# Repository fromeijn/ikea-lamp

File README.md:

# ikea-lamp
make and ikea lamp smart and awesome

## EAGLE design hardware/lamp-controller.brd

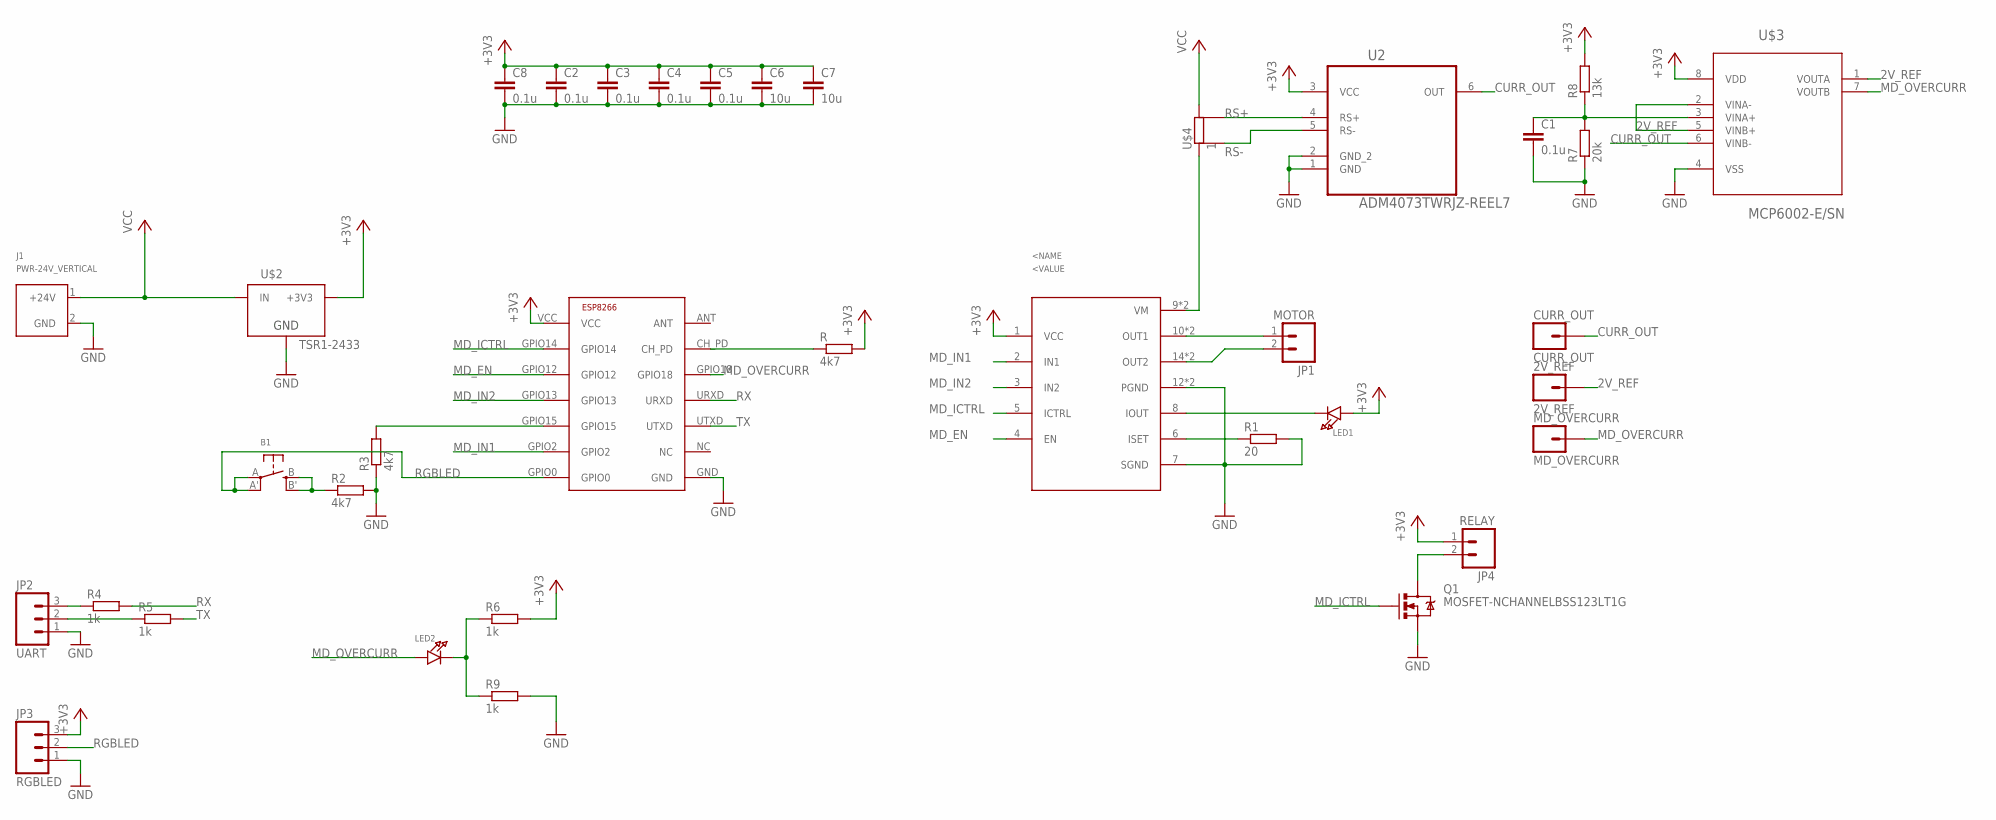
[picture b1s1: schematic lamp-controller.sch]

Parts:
2V_REF: 2V_REF; 1X01
B1: SWITCH_TACT_SMT; EVQ-Q2
C1, C2, C3, C4, C5, C8: 0.1u; C0805
C6, C7: 10u; C0805
CURR_OUT: CURR_OUT; 1X01
J1: PWR-24V_VERTICAL; PHOENIX-CONTACT-MCV-1,5/2-G-3,81
JP1: MOTOR; 1X02
JP2: UART; 1X03_LOCK
JP3: RGBLED; 1X03_LOCK
JP4: RELAY; 1X02
LED1, LED2: LED1206; CHIPLED_1206
MD_OVERCURR: MD_OVERCURR; 1X01
Q1: MOSFET-NCHANNELBSS123LT1G; SOT23
R, R2, R3: 4k7; R0805
R1: 20; R0805
R4, R5, R6, R9: 1k; R0805
R7: 20k; R0805
R8: 13k; R0805
U1: LV8400V; TSSOP16
U2: ADM4073TWRJZ-REEL7; SOT95P280X145-6N
U$1: ESP8266-03; ESP-03
U$2: TSR1-2433; TSR-1
U$3: MCP6002-E/SN; SOIC127P600X175-8N
U$4: 1; R2512

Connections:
2V_REF: 2V_REF.1, U$3.1 (VOUTA), U$3.2 (VINA-), U$3.5 (VINB+)
+3V3: C2.1, C3.1, C4.1, C5.1, C6.1, C7.1, C8.1, JP3.3, JP4.1, LED1.A, R.2, R6.2, R8.2, U1.1 (VCC), U2.3 (VCC), U$1.VCC, U$2.3 (+3V3), U$3.8 (VDD)
CURR_OUT: CURR_OUT.1, U2.6 (OUT), U$3.6 (VINB-)
GND: C1.2, C2.2, C3.2, C4.2, C5.2, C6.2, C7.2, C8.2, J1.2 (GND), JP2.1, JP3.1, Q1.2 (S), R1.2, R2.2, R3.1, R7.1, R9.2, U1.7 (SGND), U1.12 (PGND), U1.13 (PGND), U2.2 (GND_2), U$1.GND, U$2.2 (GND), U$3.4 (VSS)
MD_EN: U1.4 (EN), U$1.GPIO12
MD_ICTRL: Q1.1 (G), U1.5 (ICTRL), U$1.GPIO14
MD_IN1: U1.2 (IN1), U$1.GPIO2
MD_IN2: U1.3 (IN2), U$1.GPIO13
MD_OVERCURR: LED2.A, MD_OVERCURR.1, U$1.GPIO18, U$3.7 (VOUTB)
unnamed: LED1.C, U1.8 (IOUT)
unnamed: R1.1, U1.6 (ISET)
unnamed: B1.B (S), B1.B' (S1), R2.1
unnamed: R3.2, U$1.GPIO15
unnamed: JP1.1, U1.10 (OUT1), U1.11 (OUT1)
unnamed: JP1.2, U1.14 (OUT2), U1.15 (OUT2)
unnamed: U1.9 (VM), U1.16 (VM), U$4.1
unnamed: JP2.2, R5.1
unnamed: R.1, U$1.CH_PD
unnamed: JP2.3, R4.1
unnamed: C1.1, R7.2, R8.1, U$3.3 (VINA+)
unnamed: LED2.C, R6.1, R9.1
unnamed: JP4.2, Q1.3 (D)
RGBLED: B1.A, B1.A' (P1), JP3.2, U$1.GPIO0
RS+: U2.4 (RS+), U$4.4
RS-: U2.5 (RS-), U$4.3
RX: R4.2, U$1.URXD
TX: R5.2, U$1.UTXD
VCC: J1.1 (+24V), U$2.1 (IN), U$4.2

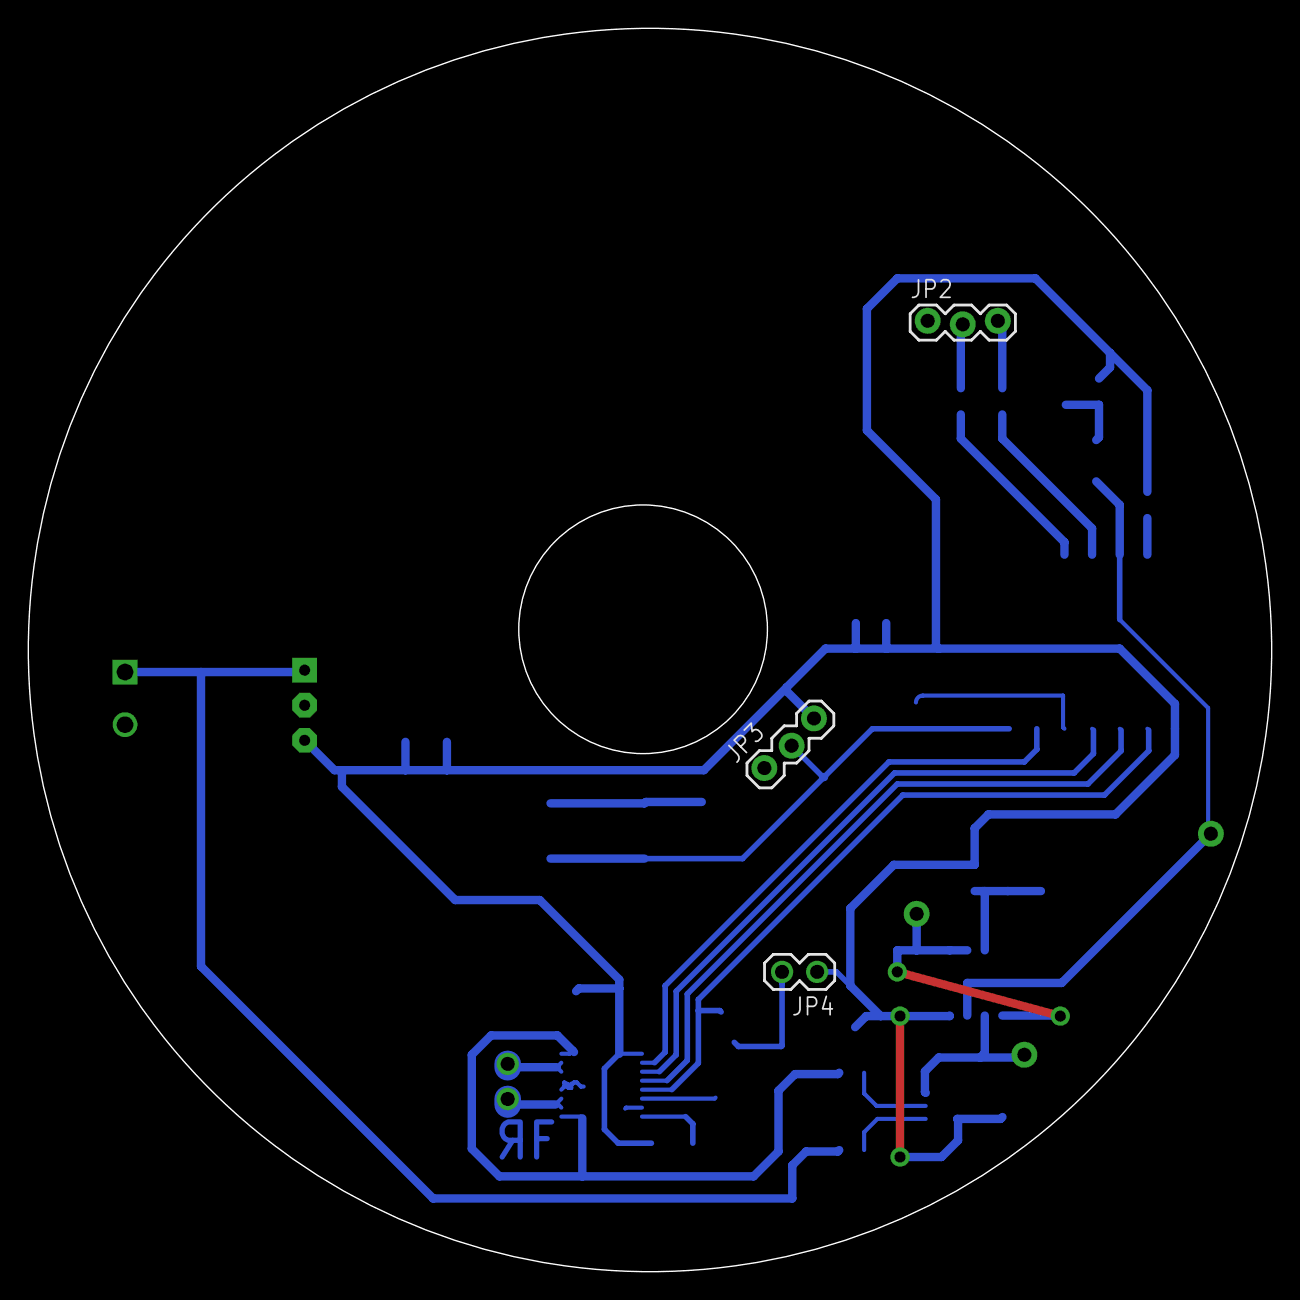
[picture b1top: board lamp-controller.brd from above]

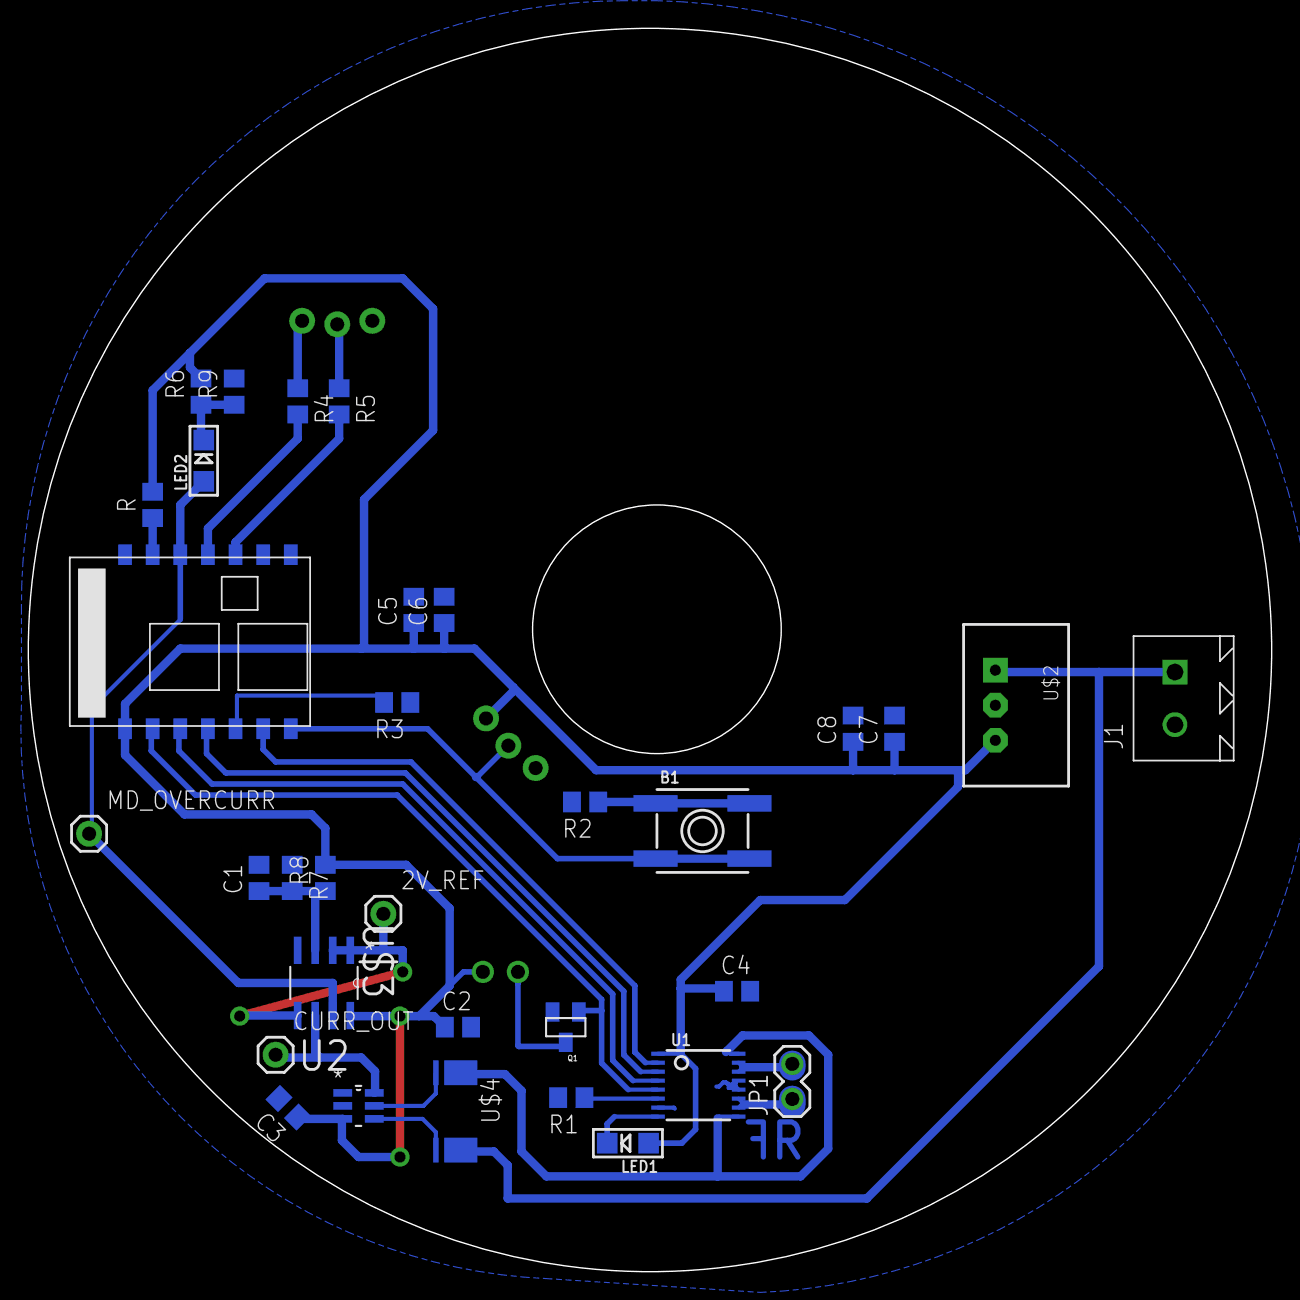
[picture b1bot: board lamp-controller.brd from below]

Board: 2 copper layers, 90.0 x 90.0 mm, 36 parts (33 on the bottom side), 28 nets.

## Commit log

2015-08-29 base

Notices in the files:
parts and their libraries:
SparkFun-Connectors: Licensing: Creative Commons ShareAlike 4.0 International - https://creativecommons.org/licenses/by-sa/4.0
microbuilder: This work is placed in the public domain, and may be freely used for commercial and non-commercial work with the following conditions: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
